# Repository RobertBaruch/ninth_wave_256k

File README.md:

Reverse engineered Ninth Wave memory expansion board for Apple IIe.

It's actually a 512k expansion.

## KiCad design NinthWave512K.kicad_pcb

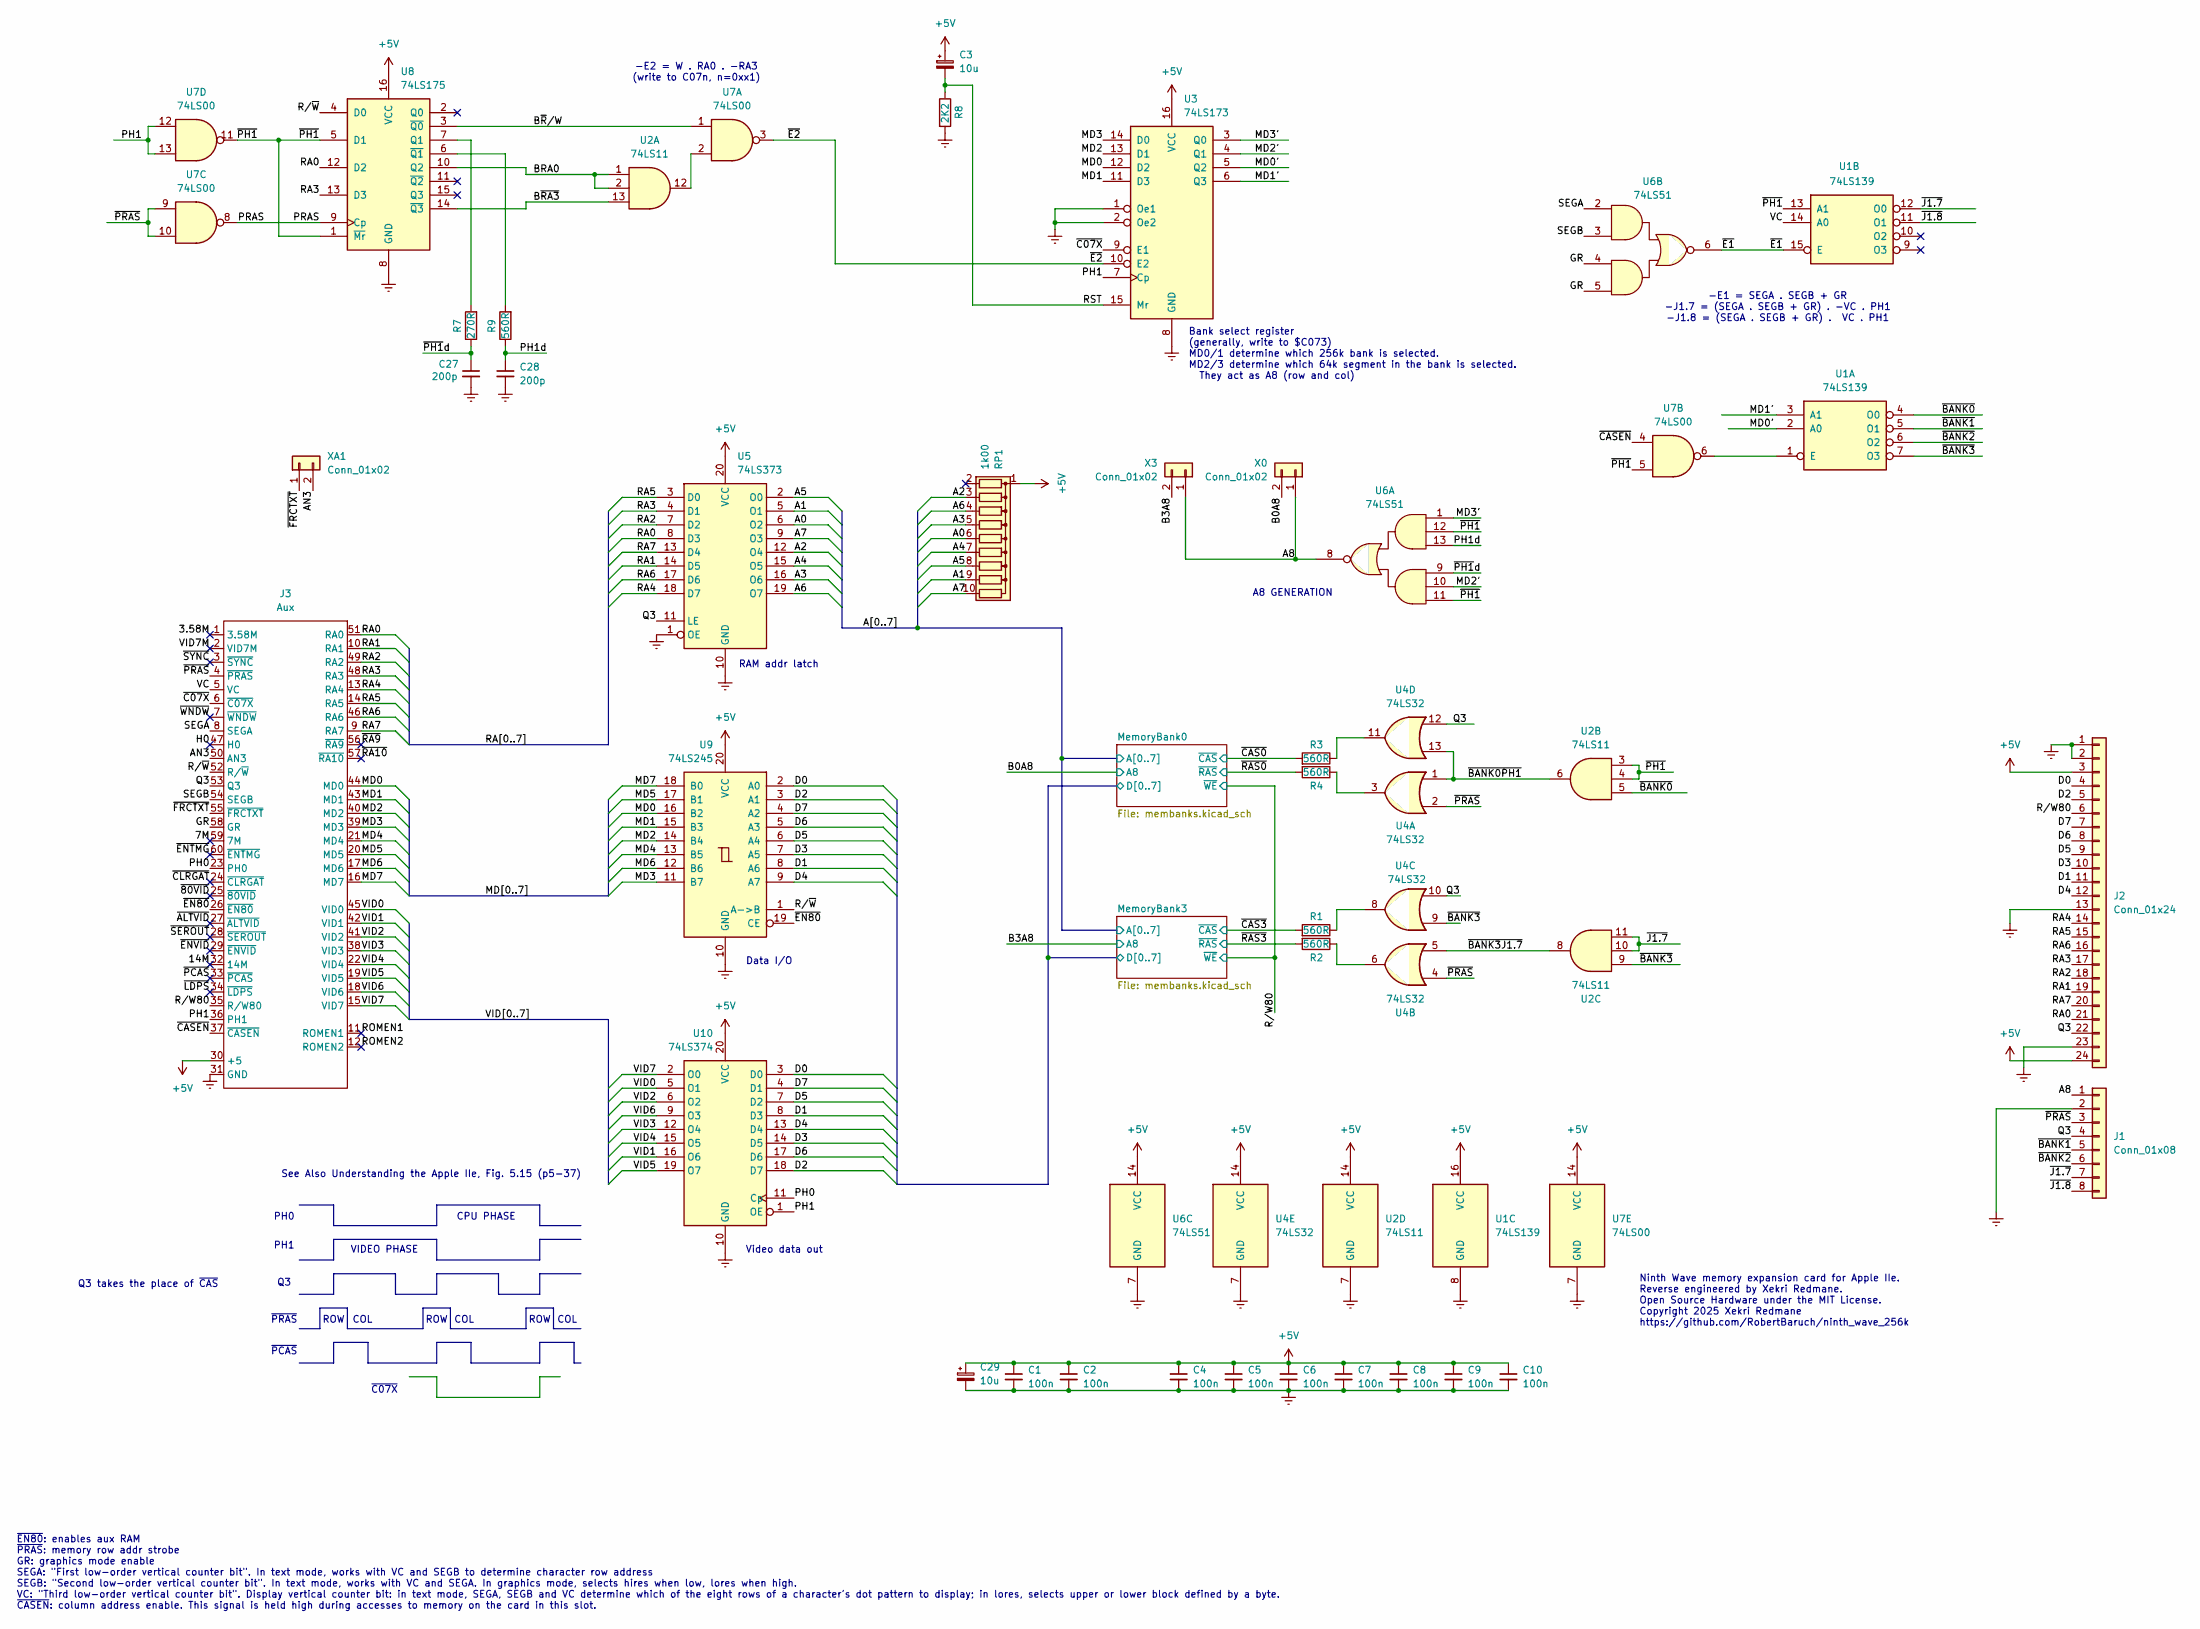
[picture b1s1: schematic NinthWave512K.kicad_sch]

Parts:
C1, C2, C4, C5, C6, C7, C8, C9, C10: 100n; C_Disc_D4.3mm_W1.9mm_P5.00mm
C3, C29: 10u; CP_Radial_Tantal_D4.5mm_P5.00mm
C27, C28: 200p; C_Disc_D4.3mm_W1.9mm_P5.00mm
J1: Conn_01x08; PinSocket_1x08_P2.54mm_Vertical
J2: Conn_01x24; PinSocket_1x24_P2.54mm_Vertical
J3: Aux; AuxPeriph
R1, R2, R3, R4, R9: 560R; R_Axial_DIN0207_L6.3mm_D2.5mm_P10.16mm_Horizontal
R7: 270R; R_Axial_DIN0207_L6.3mm_D2.5mm_P10.16mm_Horizontal
R8: 2K2; R_Axial_DIN0207_L6.3mm_D2.5mm_P10.16mm_Horizontal
RP1: 1k00; R_Array_SIP10
U1: 74LS139; DIP-16_W7.62mm
U2: 74LS11; DIP-14_W7.62mm
U3: 74LS173; DIP-16_W7.62mm
U4: 74LS32; DIP-14_W7.62mm
U5: 74LS373; DIP-20_W7.62mm
U6: 74LS51; DIP-14_W7.62mm
U7: 74LS00; DIP-14_W7.62mm
U8: 74LS175; DIP-16_W7.62mm
U9: 74LS245; DIP-20_W7.62mm
U10: 74LS374; DIP-20_W7.62mm
X0, X3: Conn_01x02; SolderJumper-2_P1.3mm_Open_TrianglePad1.0x1.5mm
XA1: Conn_01x02; SolderJumper-2_P1.3mm_Bridged_Pad1.0x1.5mm

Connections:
+5V: C1.1, C2.1, C3.1, C4.1, C5.1, C6.1, C7.1, C8.1, C9.1, C10.1, C29.1, J2.3, J2.24, J3.30 (+5), RP1.1 (common), U1.16 (VCC), U2.14 (VCC), U3.16 (VCC), U4.14 (VCC), U5.20 (VCC), U6.14 (VCC), U7.14 (VCC), U8.16 (VCC), U9.20 (VCC), U10.20 (VCC); also elsewhere on the board
/3.58M: J3.1 (3.58M)
/7M: J3.59 (7M)
/14M: J3.32 (14M)
/A0: RP1.6 (R5), U5.6 (O2); also elsewhere on the board
/A1: RP1.9 (R8), U5.5 (O1); also elsewhere on the board
/A2: RP1.3 (R2), U5.12 (O4); also elsewhere on the board
/A3: RP1.5 (R4), U5.16 (O6); also elsewhere on the board
/A4: RP1.7 (R6), U5.15 (O5); also elsewhere on the board
/A5: RP1.8 (R7), U5.2 (O0); also elsewhere on the board
/A6: RP1.4 (R3), U5.19 (O7); also elsewhere on the board
/A7: RP1.10 (R9), U5.9 (O3); also elsewhere on the board
/A8: J1.1, U6.8, X0.1, X3.1
/AN3: J3.50 (AN3), XA1.2
/B0A8: X0.2; also elsewhere on the board
/B3A8: X3.2; also elsewhere on the board
/BRA0: U2.1, U2.2, U8.10 (Q2)
/B~RA3: U2.13, U8.14 (~Q3)
/B~R/W: U7.1, U8.3 (~Q0)
/GR: J3.58 (GR), U6.4, U6.5
/H0: J3.47 (H0)
/J1.7: J1.7, U1.12 (O0), U2.10, U2.11
/J1.8: J1.8, U1.11 (O1)
/MD0: J3.44 (MD0), U3.12 (D2), U9.16 (B2)
/MD0': U1.2 (A0), U3.5 (Q2)
/MD1: J3.43 (MD1), U3.11 (D3), U9.15 (B3)
/MD1': U1.3 (A1), U3.6 (Q3)
/MD2: J3.40 (MD2), U3.13 (D1), U9.14 (B4)
/MD2': U3.4 (Q1), U6.10
/MD3: J3.39 (MD3), U3.14 (D0), U9.11 (B7)
/MD3': U3.3 (Q0), U6.1
/MD4: J3.21 (MD4), U9.13 (B5)
/MD5: J3.20 (MD5), U9.17 (B1)
/MD6: J3.17 (MD6), U9.12 (B6)
/MD7: J3.16 (MD7), U9.18 (B0)
/MemoryBank0/D0: J2.4, U9.2 (A0), U10.3 (D0); also elsewhere on the board
/MemoryBank0/D1: J2.11, U9.8 (A6), U10.8 (D3); also elsewhere on the board
/MemoryBank0/D2: J2.5, U9.3 (A1), U10.18 (D7); also elsewhere on the board
/MemoryBank0/D3: J2.10, U9.7 (A5), U10.14 (D5); also elsewhere on the board
/MemoryBank0/D4: J2.12, U9.9 (A7), U10.13 (D4); also elsewhere on the board
/MemoryBank0/D5: J2.9, U9.6 (A4), U10.7 (D2); also elsewhere on the board
/MemoryBank0/D6: J2.8, U9.5 (A3), U10.17 (D6); also elsewhere on the board
/MemoryBank0/D7: J2.7, U9.4 (A2), U10.4 (D1); also elsewhere on the board
/PH0: J3.23 (PH0), U10.11 (Cp)
/PH1: J3.36 (PH1), U3.7 (Cp), U7.12, U7.13, U10.1 (OE)
/PH1d: C28.1, R9.1, U6.13
/PRAS: U7.8, U8.9 (Cp)
/Q3: J1.4, J2.22, J3.53 (Q3), U4.10, U4.12, U5.11 (LE)
/RA0: J2.21, J3.51 (RA0), U5.8 (D3), U8.12 (D2)
/RA1: J2.19, J3.10 (RA1), U5.14 (D5)
/RA2: J2.18, J3.49 (RA2), U5.7 (D2)
/RA3: J2.17, J3.48 (RA3), U5.4 (D1), U8.13 (D3)
/RA4: J2.14, J3.13 (RA4), U5.18 (D7)
/RA5: J2.15, J3.14 (RA5), U5.3 (D0)
/RA6: J2.16, J3.46 (RA6), U5.17 (D6)
/RA7: J2.20, J3.9 (RA7), U5.13 (D4)
/ROMEN1: J3.11 (ROMEN1)
/ROMEN2: J3.12 (ROMEN2)
/RST: C3.2, R8.1, U3.15 (Mr)
/R/W80: J2.6, J3.35 (R/W80); also elsewhere on the board
/R/~W: J3.52 (R/~W), U8.4 (D0), U9.1 (A->B)
/SEGA: J3.8 (SEGA), U6.2
/SEGB: J3.54 (SEGB), U6.3
/VC: J3.5 (VC), U1.14 (A0)
/VID0: J3.45 (VID0), U10.5 (O1)
/VID1: J3.42 (VID1), U10.16 (O6)
/VID2: J3.41 (VID2), U10.6 (O2)
/VID3: J3.38 (VID3), U10.12 (O4)
/VID4: J3.22 (VID4), U10.15 (O5)
/VID5: J3.19 (VID5), U10.19 (O7)
/VID6: J3.18 (VID6), U10.9 (O3)
/VID7: J3.15 (VID7), U10.2 (O0)
/VID7M: J3.2 (VID7M)
/~80VID: J3.25 (~80VID)
/~ALTVID: J3.27 (~ALTVID)
/~BANK0PH1: U2.6, U4.1, U4.13
/~BANK0: U1.4 (O0), U2.5
/~BANK1: J1.5, U1.5 (O1)
/~BANK2: J1.6, U1.6 (O2)
/~BANK3: U1.7 (O3), U2.9, U4.9
/~C07X: J3.6 (~C07X), U3.9 (E1)
/~CAS0: R3.2; also elsewhere on the board
/~CAS3: R1.2; also elsewhere on the board
/~CASEN: J3.37 (~CASEN), U7.4
/~CLRGAT: J3.24 (~CLRGAT)
/~E1: U1.15 (E), U6.6
/~E2: U3.10 (E2), U7.3
/~EN80: J3.26 (~EN80), U9.19 (CE)
/~ENTMG: J3.60 (~ENTMG)
/~ENVID: J3.29 (~ENVID)
/~FRCTXT: J3.55 (~FRCTXT), XA1.1
/~LDPS: J3.34 (~LDPS)
/~PCAS: J3.33 (~PCAS)
/~PH1: U1.13 (A1), U2.3, U2.4, U6.11, U6.12, U7.5, U7.11, U8.1 (~Mr), U8.5 (D1)
/~PH1d: C27.1, R7.1, U6.9
/~PRAS: J1.3, J3.4 (~PRAS), U4.2, U4.4, U7.9, U7.10
/~RA9: J3.56 (~RA9)
/~RA10: J3.57 (~RA10)
/~RAS0: R4.2; also elsewhere on the board
/~RAS3: R2.2; also elsewhere on the board
/~SEROUT: J3.28 (~SEROUT)
/~SYNC: J3.3 (~SYNC)
/~WNDW: J3.7 (~WNDW)
GNDREF: C1.2, C2.2, C4.2, C5.2, C6.2, C7.2, C8.2, C9.2, C10.2, C27.2, C28.2, C29.2, J1.2, J2.1, J2.2, J2.13, J2.23, J3.31 (GND), R8.2, U1.8 (GND), U2.7 (GND), U3.1 (Oe1), U3.2 (Oe2), U3.8 (GND), U4.7 (GND), U5.1 (OE), U5.10 (GND), U6.7 (GND), U7.7 (GND), U8.8 (GND), U9.10 (GND), U10.10 (GND); also elsewhere on the board
unnamed: R1.1, U4.8
unnamed: R2.1, U4.6
unnamed: R3.1, U4.11
unnamed: R4.1, U4.3
unnamed: U1.1 (E), U7.6
unnamed: U2.8, U4.5
unnamed: U2.12, U7.2
unnamed: R7.2, U8.7 (Q1)
unnamed: R9.2, U8.6 (~Q1)

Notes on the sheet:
COL
-E1 = SEGA . SEGB + GR -J1.7 = (SEGA . SEGB + GR) . -VC . PH1 -J1.8 = (SEGA . SEGB + GR) . VC . PH1
A8 GENERATION
PH0
PH1
ROW
VIDEO PHASE
RAM addr latch
Ninth Wave memory expansion card for Apple IIe. Reverse engineered by Xekri Redmane. Open Source Hardware under the MIT License. Copyright 2025 Xekri Redmane https://github.com/RobertBaruch/ninth_wave_256k
~{PCAS}
Bank select register (generally, write to $C073) MD0/1 determine which 256k bank is selected. MD2/3 determine which 64k segment in the bank is selected. They act as A8 (row and col)
-E2 = W . RA0 . -RA3 (write to C07n, n=0xx1)
Data I/O
CPU PHASE
~{C07X}
~{PRAS}
Q3 takes the place of ~{CAS}
~{EN80}: enables aux RAM ~{PRAS}: memory row addr strobe GR: graphics mode enable SEGA: "First low-order vertical counter bit". In text mode, works with VC and SEGB to determine character row address SEGB: "Second low-order vertical counter bit". In text mode, works with VC and SEGA. In graphics mo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
Video data out
See Also Understanding the Apple IIe, Fig. 5.15 (p5-37)

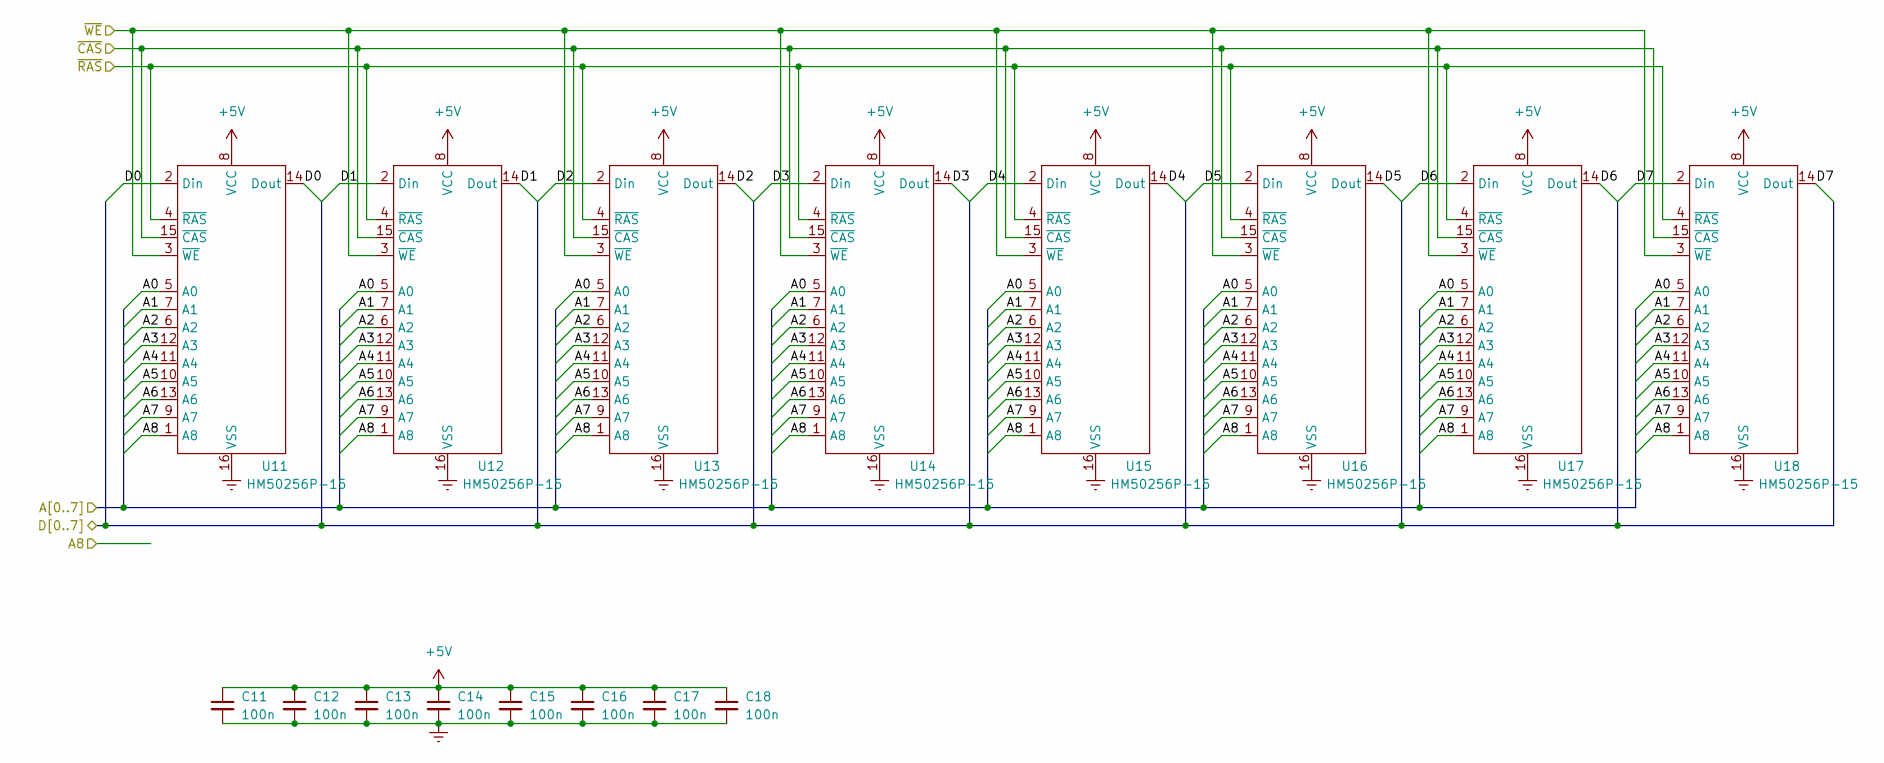
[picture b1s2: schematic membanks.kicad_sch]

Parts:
C11, C12, C13, C14, C15, C16, C17, C18: 100n; C_Disc_D4.3mm_W1.9mm_P5.00mm
U11, U12, U13, U14, U15, U16, U17, U18: HM50256P-15; DIP-16_W7.62mm_Socket

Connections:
+5V: C11.1, C12.1, C13.1, C14.1, C15.1, C16.1, C17.1, C18.1, U11.8 (VCC), U12.8 (VCC), U13.8 (VCC), U14.8 (VCC), U15.8 (VCC), U16.8 (VCC), U17.8 (VCC), U18.8 (VCC); also elsewhere on the board
/A0: U11.5 (A0), U12.5 (A0), U13.5 (A0), U14.5 (A0), U15.5 (A0), U16.5 (A0), U17.5 (A0), U18.5 (A0); also elsewhere on the board
/A1: U11.7 (A1), U12.7 (A1), U13.7 (A1), U14.7 (A1), U15.7 (A1), U16.7 (A1), U17.7 (A1), U18.7 (A1); also elsewhere on the board
/A2: U11.6 (A2), U12.6 (A2), U13.6 (A2), U14.6 (A2), U15.6 (A2), U16.6 (A2), U17.6 (A2), U18.6 (A2); also elsewhere on the board
/A3: U11.12 (A3), U12.12 (A3), U13.12 (A3), U14.12 (A3), U15.12 (A3), U16.12 (A3), U17.12 (A3), U18.12 (A3); also elsewhere on the board
/A4: U11.11 (A4), U12.11 (A4), U13.11 (A4), U14.11 (A4), U15.11 (A4), U16.11 (A4), U17.11 (A4), U18.11 (A4); also elsewhere on the board
/A5: U11.10 (A5), U12.10 (A5), U13.10 (A5), U14.10 (A5), U15.10 (A5), U16.10 (A5), U17.10 (A5), U18.10 (A5); also elsewhere on the board
/A6: U11.13 (A6), U12.13 (A6), U13.13 (A6), U14.13 (A6), U15.13 (A6), U16.13 (A6), U17.13 (A6), U18.13 (A6); also elsewhere on the board
/A7: U11.9 (A7), U12.9 (A7), U13.9 (A7), U14.9 (A7), U15.9 (A7), U16.9 (A7), U17.9 (A7), U18.9 (A7); also elsewhere on the board
/B3A8: U11.1 (A8), U12.1 (A8), U13.1 (A8), U14.1 (A8), U15.1 (A8), U16.1 (A8), U17.1 (A8), U18.1 (A8); also elsewhere on the board
/MemoryBank0/D0: U11.2 (Din), U11.14 (Dout); also elsewhere on the board
/MemoryBank0/D1: U12.2 (Din), U12.14 (Dout); also elsewhere on the board
/MemoryBank0/D2: U13.2 (Din), U13.14 (Dout); also elsewhere on the board
/MemoryBank0/D3: U14.2 (Din), U14.14 (Dout); also elsewhere on the board
/MemoryBank0/D4: U15.2 (Din), U15.14 (Dout); also elsewhere on the board
/MemoryBank0/D5: U16.2 (Din), U16.14 (Dout); also elsewhere on the board
/MemoryBank0/D6: U17.2 (Din), U17.14 (Dout); also elsewhere on the board
/MemoryBank0/D7: U18.2 (Din), U18.14 (Dout); also elsewhere on the board
/R/W80: U11.3 (~WE), U12.3 (~WE), U13.3 (~WE), U14.3 (~WE), U15.3 (~WE), U16.3 (~WE), U17.3 (~WE), U18.3 (~WE); also elsewhere on the board
/~CAS3: U11.15 (~CAS), U12.15 (~CAS), U13.15 (~CAS), U14.15 (~CAS), U15.15 (~CAS), U16.15 (~CAS), U17.15 (~CAS), U18.15 (~CAS); also elsewhere on the board
/~RAS3: U11.4 (~RAS), U12.4 (~RAS), U13.4 (~RAS), U14.4 (~RAS), U15.4 (~RAS), U16.4 (~RAS), U17.4 (~RAS), U18.4 (~RAS); also elsewhere on the board
GNDREF: C11.2, C12.2, C13.2, C14.2, C15.2, C16.2, C17.2, C18.2, U11.16 (VSS), U12.16 (VSS), U13.16 (VSS), U14.16 (VSS), U15.16 (VSS), U16.16 (VSS), U17.16 (VSS), U18.16 (VSS); also elsewhere on the board

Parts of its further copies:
C19, C20, C21, C22, C23, C24, C25, C26: 100n; C_Disc_D4.3mm_W1.9mm_P5.00mm
U19, U20, U21, U22, U23, U24, U25, U26: HM50256P-15; DIP-16_W7.62mm_Socket

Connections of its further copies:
+5V: C19.1, C20.1, C21.1, C22.1, C23.1, C24.1, C25.1, C26.1, U19.8 (VCC), U20.8 (VCC), U21.8 (VCC), U22.8 (VCC), U23.8 (VCC), U24.8 (VCC), U25.8 (VCC), U26.8 (VCC); also elsewhere on the board
/A0: U19.5 (A0), U20.5 (A0), U21.5 (A0), U22.5 (A0), U23.5 (A0), U24.5 (A0), U25.5 (A0), U26.5 (A0); also elsewhere on the board
/A1: U19.7 (A1), U20.7 (A1), U21.7 (A1), U22.7 (A1), U23.7 (A1), U24.7 (A1), U25.7 (A1), U26.7 (A1); also elsewhere on the board
/A2: U19.6 (A2), U20.6 (A2), U21.6 (A2), U22.6 (A2), U23.6 (A2), U24.6 (A2), U25.6 (A2), U26.6 (A2); also elsewhere on the board
/A3: U19.12 (A3), U20.12 (A3), U21.12 (A3), U22.12 (A3), U23.12 (A3), U24.12 (A3), U25.12 (A3), U26.12 (A3); also elsewhere on the board
/A4: U19.11 (A4), U20.11 (A4), U21.11 (A4), U22.11 (A4), U23.11 (A4), U24.11 (A4), U25.11 (A4), U26.11 (A4); also elsewhere on the board
/A5: U19.10 (A5), U20.10 (A5), U21.10 (A5), U22.10 (A5), U23.10 (A5), U24.10 (A5), U25.10 (A5), U26.10 (A5); also elsewhere on the board
/A6: U19.13 (A6), U20.13 (A6), U21.13 (A6), U22.13 (A6), U23.13 (A6), U24.13 (A6), U25.13 (A6), U26.13 (A6); also elsewhere on the board
/A7: U19.9 (A7), U20.9 (A7), U21.9 (A7), U22.9 (A7), U23.9 (A7), U24.9 (A7), U25.9 (A7), U26.9 (A7); also elsewhere on the board
/B0A8: U19.1 (A8), U20.1 (A8), U21.1 (A8), U22.1 (A8), U23.1 (A8), U24.1 (A8), U25.1 (A8), U26.1 (A8); also elsewhere on the board
/MemoryBank0/D0: U19.2 (Din), U19.14 (Dout); also elsewhere on the board
/MemoryBank0/D1: U20.2 (Din), U20.14 (Dout); also elsewhere on the board
/MemoryBank0/D2: U21.2 (Din), U21.14 (Dout); also elsewhere on the board
/MemoryBank0/D3: U22.2 (Din), U22.14 (Dout); also elsewhere on the board
/MemoryBank0/D4: U23.2 (Din), U23.14 (Dout); also elsewhere on the board
/MemoryBank0/D5: U24.2 (Din), U24.14 (Dout); also elsewhere on the board
/MemoryBank0/D6: U25.2 (Din), U25.14 (Dout); also elsewhere on the board
/MemoryBank0/D7: U26.2 (Din), U26.14 (Dout); also elsewhere on the board
/R/W80: U19.3 (~WE), U20.3 (~WE), U21.3 (~WE), U22.3 (~WE), U23.3 (~WE), U24.3 (~WE), U25.3 (~WE), U26.3 (~WE); also elsewhere on the board
/~CAS0: U19.15 (~CAS), U20.15 (~CAS), U21.15 (~CAS), U22.15 (~CAS), U23.15 (~CAS), U24.15 (~CAS), U25.15 (~CAS), U26.15 (~CAS); also elsewhere on the board
/~RAS0: U19.4 (~RAS), U20.4 (~RAS), U21.4 (~RAS), U22.4 (~RAS), U23.4 (~RAS), U24.4 (~RAS), U25.4 (~RAS), U26.4 (~RAS); also elsewhere on the board
GNDREF: C19.2, C20.2, C21.2, C22.2, C23.2, C24.2, C25.2, C26.2, U19.16 (VSS), U20.16 (VSS), U21.16 (VSS), U22.16 (VSS), U23.16 (VSS), U24.16 (VSS), U25.16 (VSS), U26.16 (VSS); also elsewhere on the board

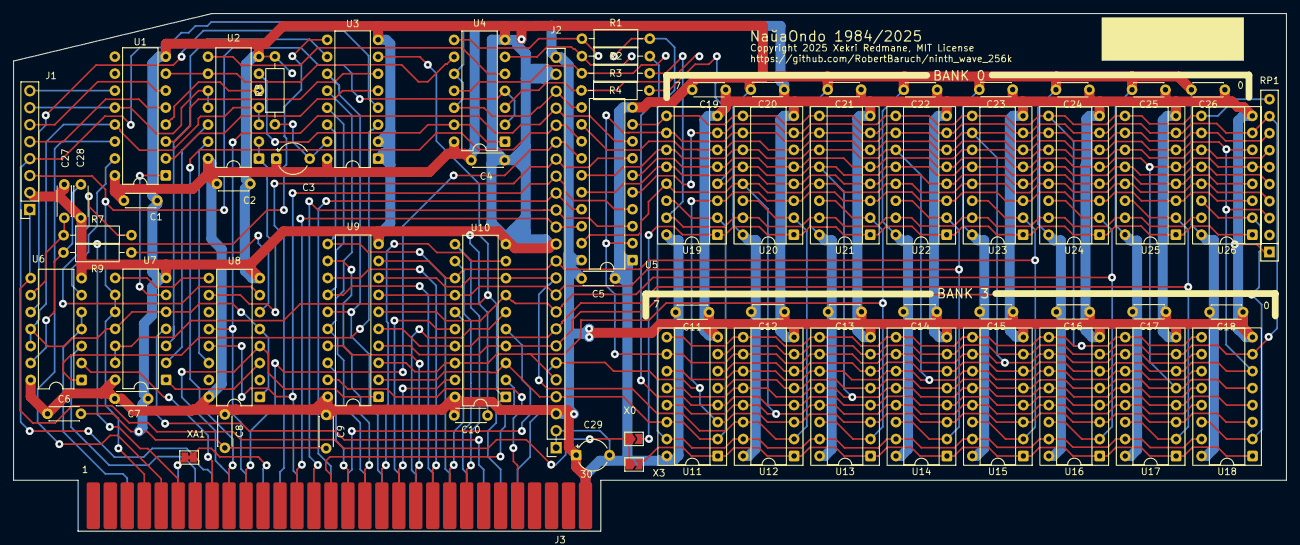
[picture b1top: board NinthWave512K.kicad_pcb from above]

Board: 2 copper layers, 190.5 x 77.5 mm, 69 parts (0 on the bottom side), 94 nets.

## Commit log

2025-06-15 Dump of project

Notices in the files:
NinthWave512K.kicad_pcb:
Copyright 2025 Xekri Redmane, MIT License
